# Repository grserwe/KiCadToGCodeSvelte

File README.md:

# KiCadToGCode (SvelteKit)

**Live at [kicadtogcode.com](https://kicadtogcode.com)** — free, no sign-up, and your design never leaves your browser.

Convert KiCad PCB designs into CNC GCode for isolation-engraving traces on copper-clad board and drilling through-holes — entirely in the browser. This app replaced the original Blazor version ([grserwe/KiCadToGCode](https://github.com/grserwe/KiCadToGCode)) on the same domain.

## Features

- Accepts a `.kicad_pcb` file (KiCad 4 through 10) or a zipped KiCad project
- Isolation-routing GCode for top and bottom copper, tool-diameter/V-bit aware, multi-pass with stepover. Passes after the first only widen the gap, so they stop wherever they would cut into a track or pad (on any net); each pass's GCode comment says how much was left out
- Drill GCode grouped per drill size, or onto the drill bits you list (each hole uses the nearest bit within a set difference, so 0.8/0.9/1.0 mm share one file), plus registration holes for double-sided flip-over machining (bottom side mirrored about the vertical centerline)
- Board cutout GCode: an end mill follows the Edge.Cuts outline (lines, arcs, circles, rectangles, polygons — chained into closed loops, with inner cutouts cut first) offset by the cutter radius, climb milling in depth passes, leaving holding tabs on the straight edges
- All pad shapes: circle, oval, rect, roundrect (incl. chamfered), trapezoid, and custom polygon (e.g. hexagonal) pads; ground pads get thermal-relief gaps
- Copper pours (KiCad zones) for free: on a layer with a pour, the pour's net is left uncut, so all the copper the bit never touches becomes that net. Its tracks get no isolation, its pads join the copper with thermal spokes, solidly, or not at all, following the zone's pad-connection setting and any per-pad override (vias always solid), and everything else is isolated as usual
- SVG preview of both board sides: copper, engraving paths, drills, registration holes, zoom/pan
- GCode viewer: replays each generated program the way a GRBL controller would, drawing cuts at the tool's real width, rapids, and plunges over the designed copper (mapped into machine coordinates), with a move-by-move step-through and checks for rapids with the tool down, inconsistent arcs, cutting with the spindle off, and missing feed rates or units
- Configurable CNC settings (feeds, speeds, depths, origin, units), persisted in the browser
- Clearance-aware minimum widths: thin traces and small pads are widened to your configured minimums (so copper doesn't peel during machining), capped automatically wherever copper on another net is too close — widening can never cause a short, and blocked spots are reported
- Silkscreen SVG for laser marking: the top (and bottom) silkscreen drawings and text as a millimetre-sized SVG ready for LightBurn, with Print and Cut alignment targets on two drilled holes, plus the board outline and registration holes on their own colour/layer
- All processing client-side in a Web Worker — your design never leaves your machine
- Recoverable problems surface as warnings (oval slot holes, curved traces, inner layers, an isolation cut wider than a pour's clearance) instead of failures

## How the toolpaths are made

1. **Parse** — a character-level S-expression tokenizer reads the `.kicad_pcb` into a board model in board-local, Y-up millimeter coordinates. Legacy (`module`) and modern (`footprint`) dialects both supported.
2. **Offset** — every track becomes two parallel lines at `width/2 + tool radius`; where tracks meet, the lines are mitered or joined by angular adjacency. A track that runs through a pad (a component lead sitting mid-track) is first split at that pad so both pieces end inside it.
3. **Pad isolation** — circular pads become arcs with gaps where tracks enter; other shapes build an outline (lines + corner arcs, inflated exactly by the tool radius) and gaps are cut out as perimeter intervals.
   Thermal-relief pads keep four 45° spokes uncut as well.
4. **Extra passes** — passes 2 and up are the same toolpath at a larger offset, built feature by feature, so where two features are closer than the full cut an outer pass of one would run into the other. Each such path is sampled every 0.02 mm against every track and pad on the layer (inflated by the tool radius), the boundaries are refined by bisection, and only the clear pieces are kept (pieces under 0.1 mm are dropped). The pour's undesigned copper is not protected: widening the gap into it is what the extra passes are for.
5. **Emit** — a greedy nearest-neighbour walk orders the segments, then the transform pipeline applies side mirroring, user flips, XY-zero placement, and unit conversion before writing GRBL-safe GCode (G0/G1/G2/G3, M3/M5).

## Board cutout

The profile program (`<board>-profile.txt`) cuts the board free, so it runs last. The Edge.Cuts drawings are chained end to end into closed loops (endpoints within 0.05 mm join; circles and polygons are loops already), the largest loop is the board boundary and loops inside it are holes. Every loop is wound so the material is on its left — boundary counter-clockwise, holes clockwise — and then offset to its right by the cutter radius: straight edges shift, outward arcs grow, inward arcs shrink, convex corners get an arc around the vertex and concave corners are trimmed to the intersection. Holes are cut before the boundary. With the bottom side mirrored, the loop direction is reversed so the machine still climb mills.

The cut is made in depth passes (total depth ÷ depth per pass, in output units). On the passes below the tab top, the cutter lifts to the tab height over each tab, which are spread evenly along the straight edges and kept clear of the corners. A board with no closed outline is cut along the rectangle of its extents, with a warning; an inside curve tighter than the cutter is reported and cut as a cusp.

## Silkscreen for the laser

The silkscreen output is an SVG, not GCode: LightBurn imports SVG and plans the laser job itself. The parser keeps every `fp_*`/`gr_*` drawing on F.SilkS, B.SilkS and Edge.Cuts (lines, arcs, circles, rectangles, polygons, in both the modern three-point and the KiCad 4/5 centre-and-angle arc dialects), placed with the same footprint transform the pads use. The SVG uses LightBurn's first three palette colours so each kind of geometry arrives on its own layer:

- **black** — silk lines as centreline vectors (a diode laser's spot is about a silk line's width, so a single pass draws them at the right size)
- **blue** — filled silk shapes, to be cut in Fill mode
- **red** — the board outline and the registration holes, for aligning the burn to the milled board; set that layer's output off before burning

The bottom side is mirrored left-over-right (the face the laser sees), the same convention as the bottom isolation GCode. Silkscreen _text_ (reference designators, labels) is parsed but not drawn yet — KiCad draws text with its own stroke font, which the engine doesn't carry — and a warning lists how many items were left out.

## Copper pours

Isolation milling never removes the copper between cuts, so it is all still on the board, joined up. On a layer with a KiCad zone, that leftover copper is used as the pour:

- tracks on the pour's net are not cut around (they are part of the pour);
- pads on the pour's net get the zone's pad connection: thermal reliefs (four uncut spokes, plus gaps where their tracks enter), solid (no cut at all), or none (a ring with gaps only for their tracks). A pad's own `zone_connect` overrides the zone; vias are always solid, as in KiCad;
- everything on other nets is isolated as before, including ground-named pads that are not on the pour's net.

The milled pour covers more than KiCad's fill: it reaches every bit of copper left uncut, beyond the zone outline, and it keeps copper islands KiCad would have removed, which just float. As long as the isolation cut (tool diameter plus the extra passes) is no wider than the zone clearance, the cuts lie inside KiCad's clearance gaps, so every connection KiCad's fill makes is still there; a wider cut is reported. A layer has only one sheet of leftover copper, so it can carry only one pour net: when zones for several nets share a layer, the one with the largest area is used and the others are reported as ignored. Layers without a zone keep the old behaviour (ground-named pads get thermal reliefs; every track is isolated).

## Roadmap (not yet supported)

- Several pour nets on one layer (split planes)
- Curved (arc) traces
- Inner layers (4+ layer boards)

## Development

```bash
npm install
npm run dev        # dev server
npm run test       # vitest unit tests
npm run check      # svelte-check / type-check
npm run lint       # prettier + eslint
npm run build      # production build (adapter-node)
```

## Feedback form

"Send feedback" in the footer (and "Report a problem" next to the output) opens a dialog that emails the message to the developer. The user's PCB file is attached by default — they can untick it — and they may add screenshots or other files. The current settings and any warnings on screen go into the email body. `POST /api/feedback` receives the form and sends it with nodemailer over SMTP, rate-limited per client and guarded by a honeypot field; without SMTP credentials it logs the message in dev and answers 503 in production.

Configure with `SMTP_HOST`, `SMTP_USER`, `SMTP_PASS` (optionally `SMTP_PORT`, default 465), `EMAIL_FROM` and `FEEDBACK_TO` — see `.env.example`. Production uses Resend's SMTP relay with a sender on the verified `kicadtogcode.com` domain. The Dockerfile raises adapter-node's `BODY_SIZE_LIMIT` to 25 MB so attachments fit.

## Usage counts

Anonymous, cookie-free counts go to [GoatCounter](https://www.goatcounter.com): page views, plus three events, `board-converted`, `sample-converted` and `output-downloaded`. Regenerating after a settings change isn't counted. `src/lib/analytics.ts` only ever sends those fixed names, never anything from the board, including its name. Results are at [grserwe.goatcounter.com](https://grserwe.goatcounter.com).

The site code comes from `PUBLIC_GOATCOUNTER_CODE`, set in `fly.toml`. Without it nothing loads, and the note on the landing page saying what is counted disappears too. GoatCounter's script also ignores localhost, so local development never adds to the numbers.

## Architecture

- **SvelteKit + TypeScript + Tailwind 4**, `adapter-node`, no database, no auth. The only server code is `src/routes/api/feedback/` and `src/lib/server/email.ts`.
- The conversion engine is a pure, framework-free TS library in `src/lib/engine/` (`sexpr/` tokenizer → `parser/` → `model/` → `geometry/` → `toolpath/` → `gcode/`, plus `profile/` for the board cutout and `silkscreen/` for the laser SVG), runnable in the browser worker and in vitest.
- Deployed on [Fly.io](https://fly.io) via GitHub Actions (`.github/workflows/deploy.yml`): checks on every push/PR, deploy on master.

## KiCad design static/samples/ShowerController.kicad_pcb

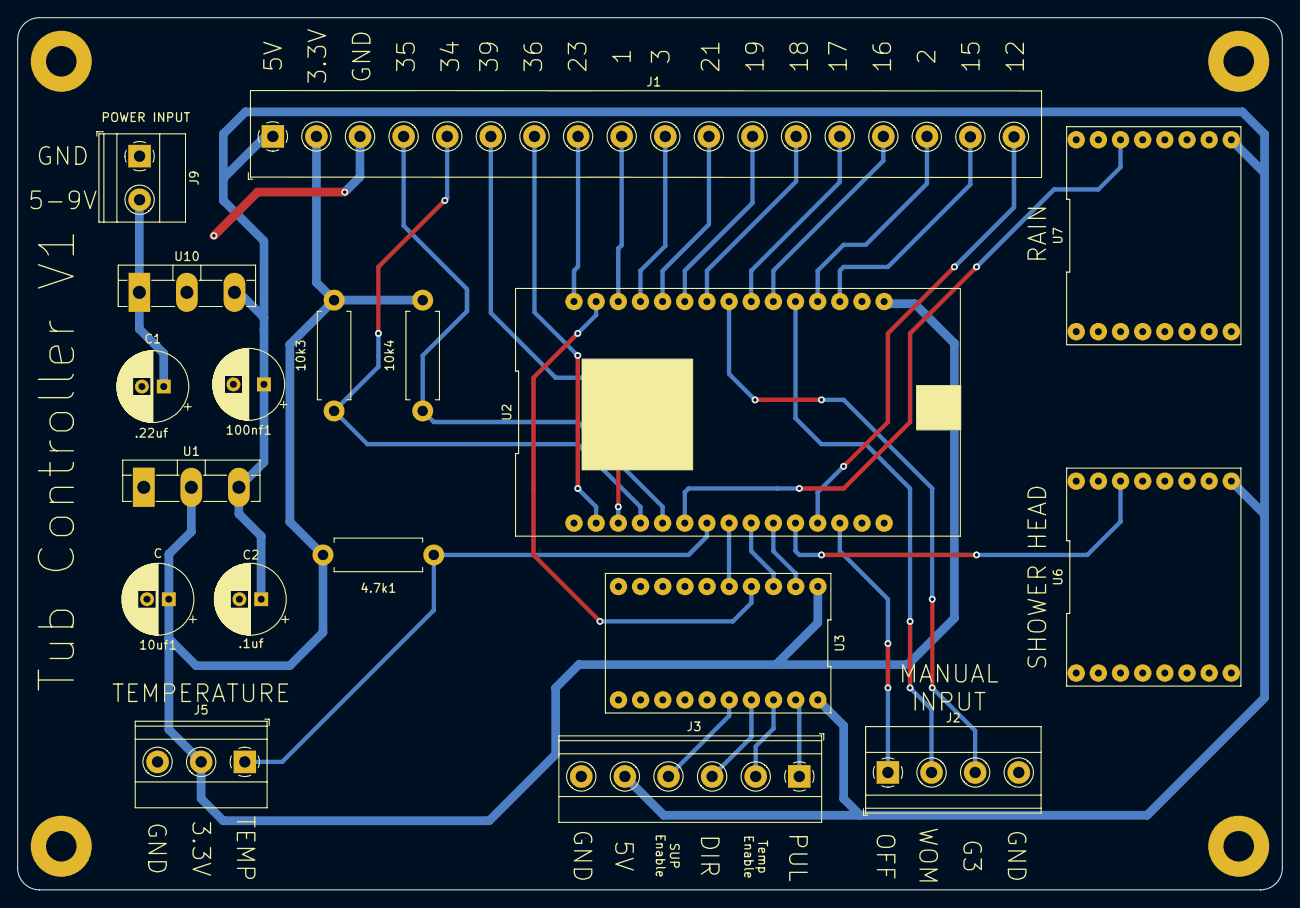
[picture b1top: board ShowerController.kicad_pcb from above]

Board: 2 copper layers, 145.0 x 100.0 mm, 22 parts (0 on the bottom side), 33 nets.

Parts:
4.7k1, 10k3, 10k4: R; R_Axial_DIN0411_L9.9mm_D3.6mm_P12.70mm_Horizontal
10uf1: C; CP_Radial_D8.0mm_P2.50mm
100nf1: C; CP_Radial_D8.0mm_P3.50mm
C1: .22uf; CP_Radial_D8.0mm_P2.50mm
C2: .1uf; CP_Radial_D8.0mm_P2.50mm
H1, H2, H3, H4: MountingHole; MountingHole_3.5mm_Pad
J1: Screw_Terminal_01x18; TerminalBlock_Phoenix_MKDS-1,5-16_1x16_P5.00mm_Horizontal
J2: Screw_Terminal_01x04; TerminalBlock_Phoenix_MKDS-1,5-4_1x04_P5.00mm_Horizontal
J3: Screw_Terminal_01x06; TerminalBlock_Phoenix_MKDS-1,5-6_1x06_P5.00mm_Horizontal
J5: Screw_Terminal_01x03; TerminalBlock_Phoenix_MKDS-1,5-3_1x03_P5.00mm_Horizontal
J9: Screw_Terminal_01x02; TerminalBlock_Phoenix_MKDS-1,5-2_1x02_P5.00mm_Horizontal
U1: LD33v; TO-3P-3_Vertical
U2: ESP32S-DEVKITV1-30Pin; ESP32-DevKitV1-30Pin
U3: TXS0108E; DIP-20_512
U6, U7: D1Relay; D1Shield
U10: L7805; TO-3P-3_Vertical

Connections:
GND: 10uf1.2, 100nf1.2, C1.2, C2.2, J1.3, J2.4, J3.6, J5.3, J9.1, U1.1 (GND), U2.14 (GND), U2.17 (GND), U3.11 (GND), U6.10 (GND), U7.10 (GND), U10.2 (GND)
unnamed: 4.7k1.1, J5.1, U2.7 (GPIO33)
unnamed: 10k3.1, J1.5, U2.4 (GPIO34)
unnamed: 4.7k1.2, 10k3.2, 10k4.2, 10uf1.1, J1.2, J5.2, U1.2 (VO), U2.16 (3v3), U3.1 (VA)
unnamed: 10k4.1, J1.4, U2.5 (GPIO35)
unnamed: 100nf1.1, C2.1, J1.1, J3.5, U1.3 (VI), U3.20 (VB), U6.9 (5V), U7.9 (5V), U10.3 (OUT)
unnamed: C1.1, J9.2, U10.1 (IN)
unnamed: J1.6, U2.3 (GPIO39)
unnamed: J1.7, U2.2 (GPIO36)
unnamed: J1.8, U2.30 (GPIO23)
unnamed: J1.9, U2.28 (GPIO1)
unnamed: J1.10, U2.27 (GPIO3)
unnamed: J1.11, U2.26 (GPIO21)
unnamed: J1.12, U2.25 (GPIO19)
unnamed: J1.13, U2.24 (GPIO18)
unnamed: J1.14, U2.22 (GPIO17)
unnamed: J1.15, U2.21 (GPIO16)
unnamed: J1.16, U2.19 (GPIO2)
unnamed: J1.17, U2.18 (GPIO15)
unnamed: J1.18, U2.12 (GPIO12)
unnamed: J2.1, U2.13 (GPIO13)
unnamed: J2.2, U2.20 (GPIO4)
unnamed: J2.3, U2.23 (GPIO5)
unnamed: J3.1, U3.19 (B1)
unnamed: J3.2, U3.18 (B2)
unnamed: J3.3, U3.17 (B3)
unnamed: J3.4, U3.16 (B4)
unnamed: U2.6 (GPIO32), U7.14 (D1)
unnamed: U2.8 (GPIO25), U3.5 (A4)
unnamed: U2.9 (GPIO26), U3.3 (A2)
unnamed: U2.10 (GPIO27), U3.2 (A1)
unnamed: U2.11 (GPIO14), U6.14 (D1)
unnamed: U2.29 (GPIO22), U3.4 (A3)
